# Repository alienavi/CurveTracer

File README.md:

# CurveTracer
This repository contains all the design files and code related to Semiconductor Curve Tracer made at CEDT, NSIT.
The different versions of Curve Tracer made are :

  - Analog Based (Oscillosccope Only)
  - Analog Based (with Arduino)
  - Arduino Only

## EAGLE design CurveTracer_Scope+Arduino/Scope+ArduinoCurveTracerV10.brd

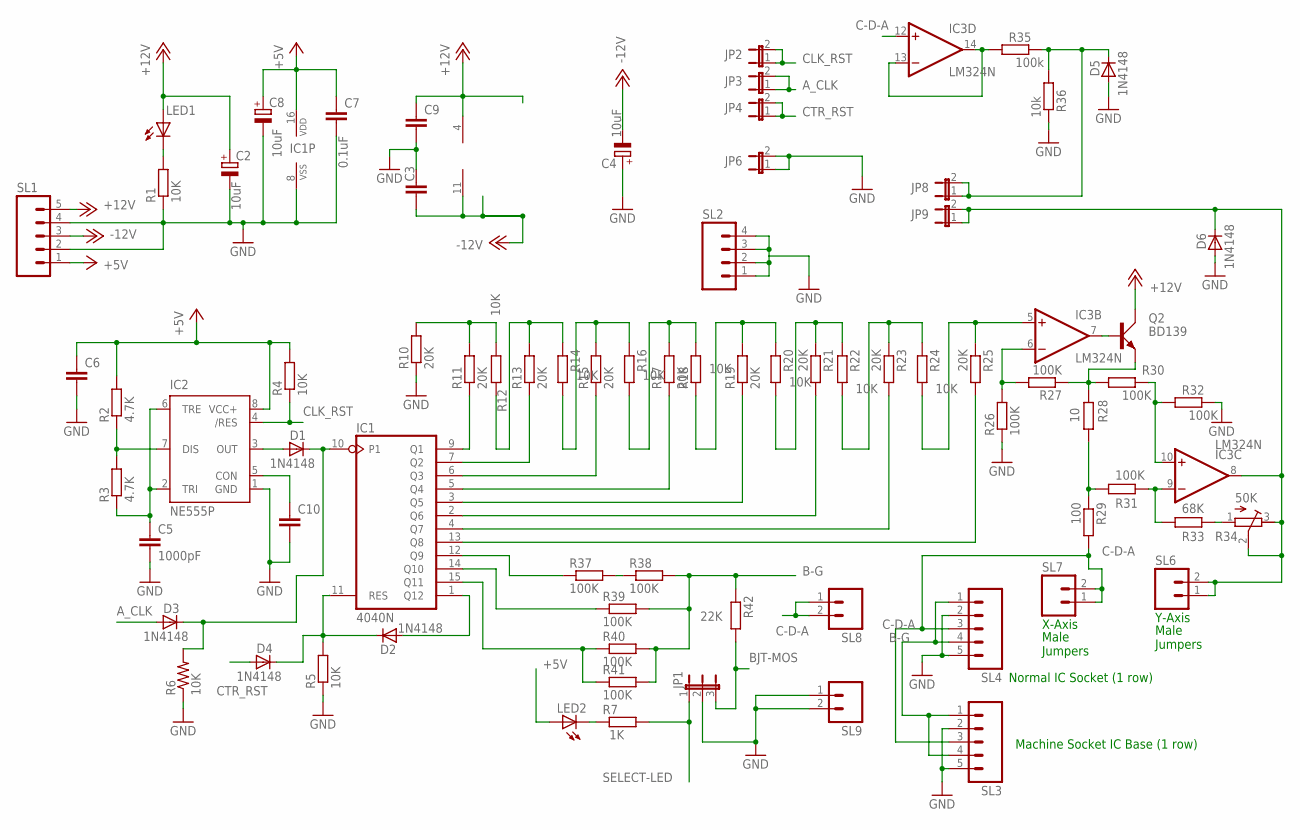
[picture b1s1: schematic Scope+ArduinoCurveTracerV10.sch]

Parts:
C2, C4, C8: 10uF; E2-5
C3, C6, C7, C9, C10: 0.1uF; C025-024X044
C5: 1000pF; C025-025X050
D1, D2, D3, D4, D5: 1N4148; DO35-7
D6: 1N4148; DO35-10
IC1: 4040N; DIL16
IC2: NE555P; DIL-08
IC3: LM324N; DIL14
JP1: JP2E; JP2
JP2, JP3, JP4, JP6, JP8, JP9: JP1E; JP1
LED1, LED2: LED3MM
Q2: BD139; TO126AV
R1, R4, R5, R6, R12, R14, R16, R18, R20, R22, R24: 10K; 0204/7
R2, R3: 4.7K; 0204/7
R7: 1K; 0204/7
R10, R11, R13, R15, R17, R19, R21, R23, R25: 20K; 0204/7
R26, R27, R31, R32, R37, R38, R39, R40, R41: 100K; 0204/7
R28: 10; 0207/10
R29: 100; 0309/12
R30: 100K; 0207/10
R33: 68K; 0204/7
R34: 50K; RTRIM64W
R35: 100k; 0204/7
R36: 10k; 0204/7
R42: 22K; 0204/7
SL1, SL3, SL4: M05; 05P
SL2: M04; 04P
SL6, SL7, SL8, SL9: M02; 02P

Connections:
+5V: C6.1, C7.1, C8.+, IC1.16 (VDD), IC2.8 (VCC+), LED2.A, R2.2, R4.2, SL1.1
+12V: C2.+, C9.1, IC3.4 (V+), LED1.A, Q2.C, SL1.5
-12V: C3.2, C4.-, IC3.11 (V-), SL1.3
A_CLK: D3.A, JP3.1, JP3.2
B-G: R38.2, R39.2, R40.2, R41.2, R42.1, SL3.1, SL3.4, SL4.1, SL4.4
BJT-MOS: JP1.3, R42.2
C-D-A: IC3.12 (+IN), R29.2, SL3.3, SL4.3, SL7.1, SL7.2, SL8.1, SL8.2
CLK_RST: IC2.4 (/RES), JP2.1, JP2.2, R4.1
CTR_RST: D4.A, JP4.1, JP4.2
GND: C2.-, C3.1, C4.+, C5.2, C6.2, C7.2, C8.-, C9.2, C10.2, D5.A, D6.A, IC1.8 (VSS), IC2.1 (GND), JP1.2, JP6.1, JP6.2, R1.1, R5.1, R6.1, R10.1, R26.1, R32.2, R36.2, SL1.2, SL1.4, SL2.1, SL2.2, SL2.3, SL2.4, SL3.2, SL3.5, SL4.2, SL4.5, SL9.1, SL9.2
unnamed: IC3.10 (+IN), R30.2, R32.1
unnamed: C10.1, IC2.5 (CON)
unnamed: R10.2, R11.2, R12.1
unnamed: D2.A, IC1.1 (Q12)
unnamed: R12.2, R13.2, R14.1
unnamed: R14.2, R15.2, R16.1
unnamed: R16.2, R17.2, R18.2
unnamed: R18.1, R19.2, R20.1
unnamed: R20.2, R21.1, R22.1
unnamed: IC1.9 (Q1), R11.1
unnamed: IC1.7 (Q2), R13.1
unnamed: IC1.6 (Q3), R15.1
unnamed: IC1.5 (Q4), R17.1
unnamed: IC1.3 (Q5), R19.1
unnamed: IC1.2 (Q6), R21.2
unnamed: IC1.4 (Q7), R23.2
unnamed: IC1.13 (Q8), R25.2
unnamed: R22.2, R23.1, R24.1
unnamed: IC3.5 (+IN), R24.2, R25.1
unnamed: R37.2, R38.1
unnamed: IC1.14 (Q10), R39.1
unnamed: IC1.12 (Q9), R37.1
unnamed: IC3.9 (-IN), R31.2, R33.1
unnamed: Q2.E, R27.1, R28.2, R30.1
unnamed: LED1.K (C), R1.2
unnamed: IC3.6 (-IN), R26.2, R27.2
unnamed: IC3.7 (OUT), Q2.B
unnamed: D1.C, D3.C, IC1.10 (P1), R6.2
unnamed: IC1.15 (Q11), R40.1, R41.1
unnamed: LED2.K (C), R7.1
unnamed: R28.1, R29.1, R31.1
unnamed: D1.A, IC2.3 (OUT)
unnamed: D2.C, D4.C, IC1.11 (RES), R5.2
unnamed: IC2.7 (DIS), R2.1, R3.2
unnamed: C5.1, IC2.2 (TRI), IC2.6 (TRE), R3.1
unnamed: D6.C, IC3.8 (OUT), JP9.1, JP9.2, R34.2 (S), R34.3 (A), SL6.1, SL6.2
unnamed: D5.C, JP8.1, JP8.2, R35.2, R36.1
unnamed: IC3.13 (-IN), IC3.14 (OUT), R35.1
unnamed: R33.2, R34.1 (E)
SELECT-LED: JP1.1, R7.2

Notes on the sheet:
X-Axis
Y-Axis
Male Jumpers
Machine Socket IC Base (1 row)
Normal IC Socket (1 row)

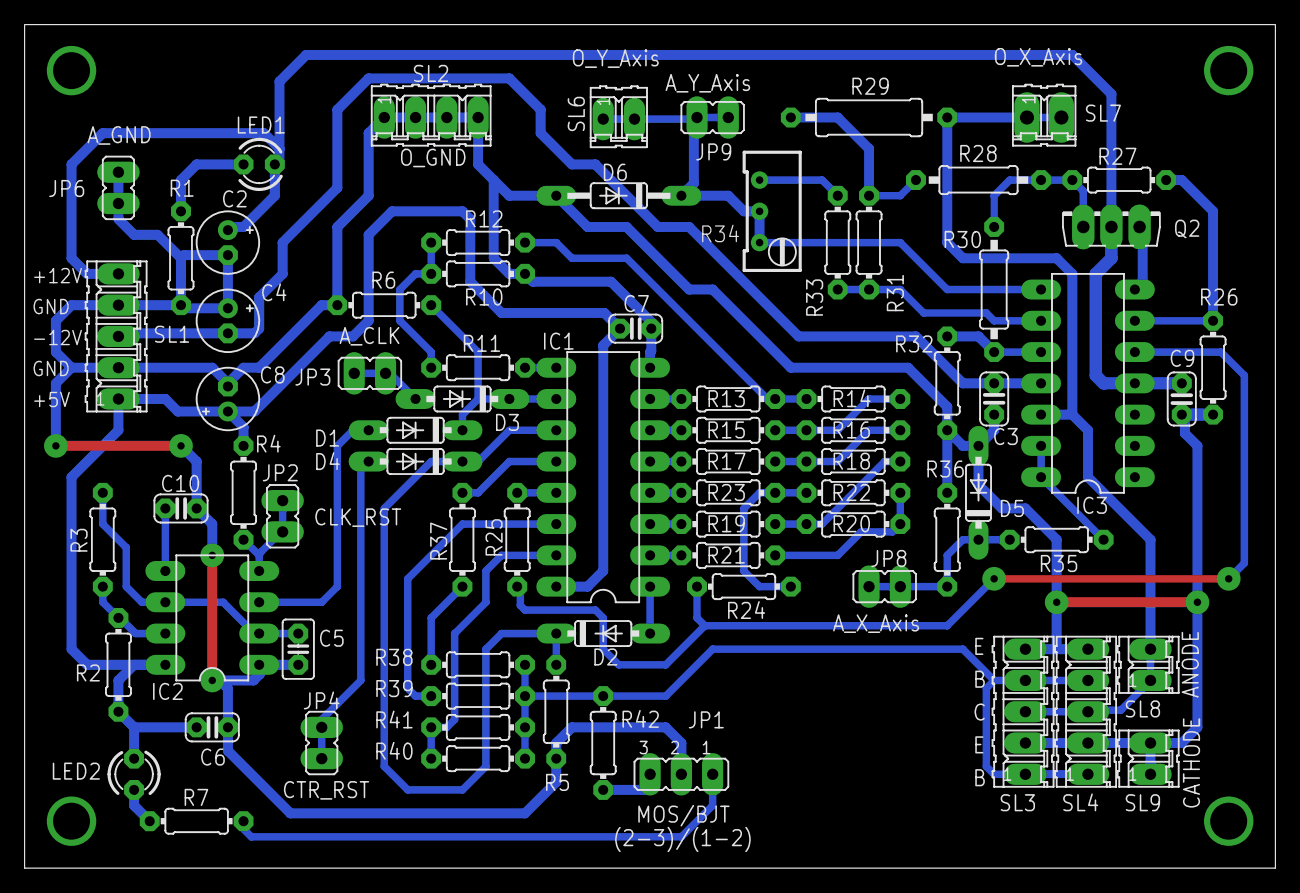
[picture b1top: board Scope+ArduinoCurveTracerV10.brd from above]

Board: 2 copper layers, 101.6 x 68.5 mm, 76 parts (0 on the bottom side), 50 nets.

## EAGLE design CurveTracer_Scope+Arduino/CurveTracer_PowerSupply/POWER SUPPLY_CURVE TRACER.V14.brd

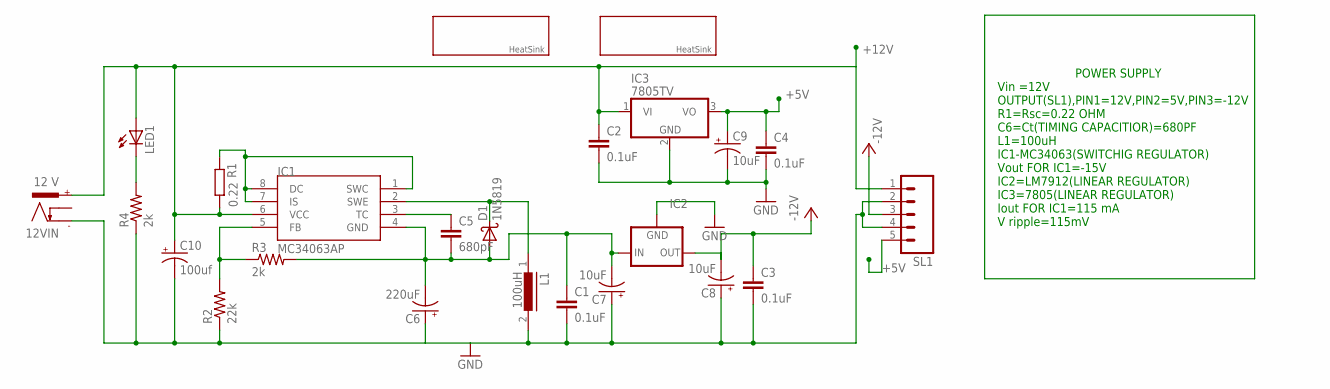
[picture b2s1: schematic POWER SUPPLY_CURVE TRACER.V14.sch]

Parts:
12VIN: 12 V; NEB21R
C1, C2, C3, C4: 0.1uF; C025-025X050
C5: 680pF; C025-025X050
C6: 220uF; E2,5-7
C7, C8, C9: 10uF; E2,5-6
C10: 100uf; E2,5-7
D1: 1N5819; DO41-10
IC1: MC34063AP; DIL08
IC2: 79XXS
IC3: 7805TV; TO220V
L1: 100uH; 82114R
LED1: LED3MM
R1: 0.22; 0617/17
R2: 22k; 0207/7
R3: 2k; 0204/7
R4: 2k; 0207/7
SL1: M05; 05P
U$1: HEATSINKMEDIUM; HEATSINK-MED
U$2: HEATSINKSMALL; HEATSINK-SML

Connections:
+5V: C4.1, C9.+, IC3.3 (VO), SL1.5
+12V: 12VIN.+, C2.1, C10.+, IC1.6 (VCC), IC3.1 (VI), LED1.A, R1.2, SL1.1
GND: 12VIN.-, C1.2, C2.2, C3.2, C4.2, C6.+, C7.+, C8.+, C9.-, C10.-, IC2.GND, IC3.2 (GND), L1.2, R2.1, R4.1, SL1.2, SL1.4
unnamed: IC1.5 (FB), R2.2, R3.1
unnamed: C1.1, C5.2, C6.-, C7.-, D1.A, IC1.4 (GND), IC2.IN, R3.2
unnamed: C5.1, IC1.3 (TC)
unnamed: D1.C, IC1.2 (SWE), L1.1
unnamed: LED1.K (C), R4.2
unnamed: IC1.1 (SWC), IC1.7 (IS), IC1.8 (DC), R1.1
VCC: C3.1, C8.-, IC2.OUT, SL1.3

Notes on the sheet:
POWER SUPPLY Vin =12V OUTPUT(SL1),PIN1=12V,PIN2=5V,PIN3=-12V R1=Rsc=0.22 OHM C6=Ct(TIMING CAPACITIOR)=680PF L1=100uH IC1-MC34063(SWITCHIG REGULATOR) Vout FOR IC1=-15V IC2=LM7912(LINEAR REGULATOR) IC3=7805(LINEAR REGULATOR) Iout FOR IC1=115 mA V ripple=115mV

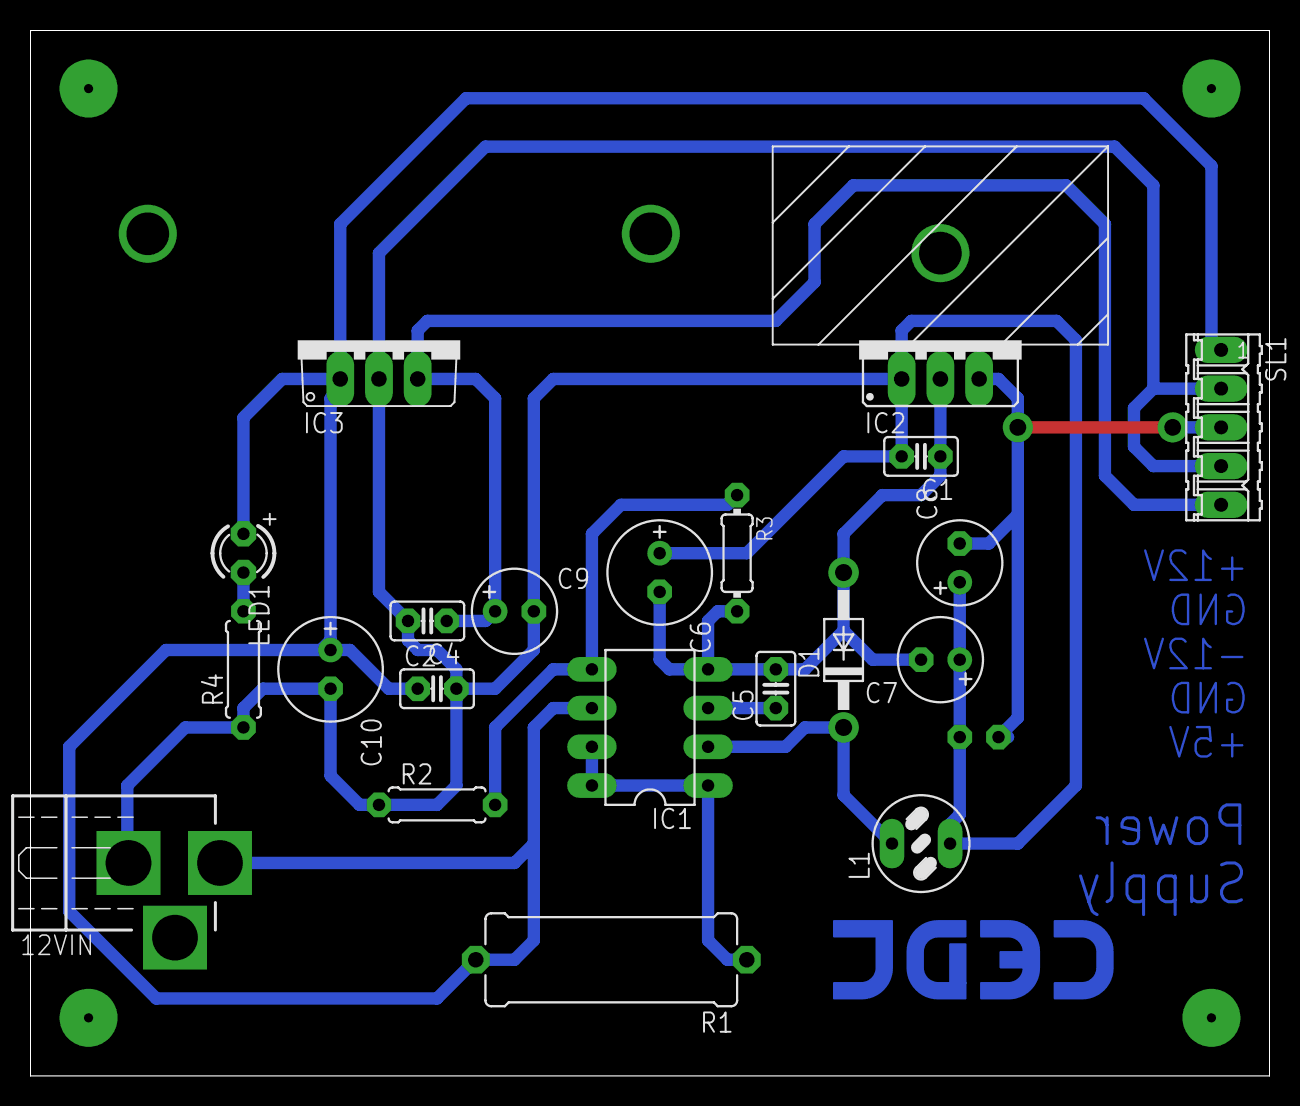
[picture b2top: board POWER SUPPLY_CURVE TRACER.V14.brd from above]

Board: 2 copper layers, 81.3 x 68.6 mm, 25 parts (1 on the bottom side), 10 nets.

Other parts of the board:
U$3: LOGO-CEDT-BOT-18MM

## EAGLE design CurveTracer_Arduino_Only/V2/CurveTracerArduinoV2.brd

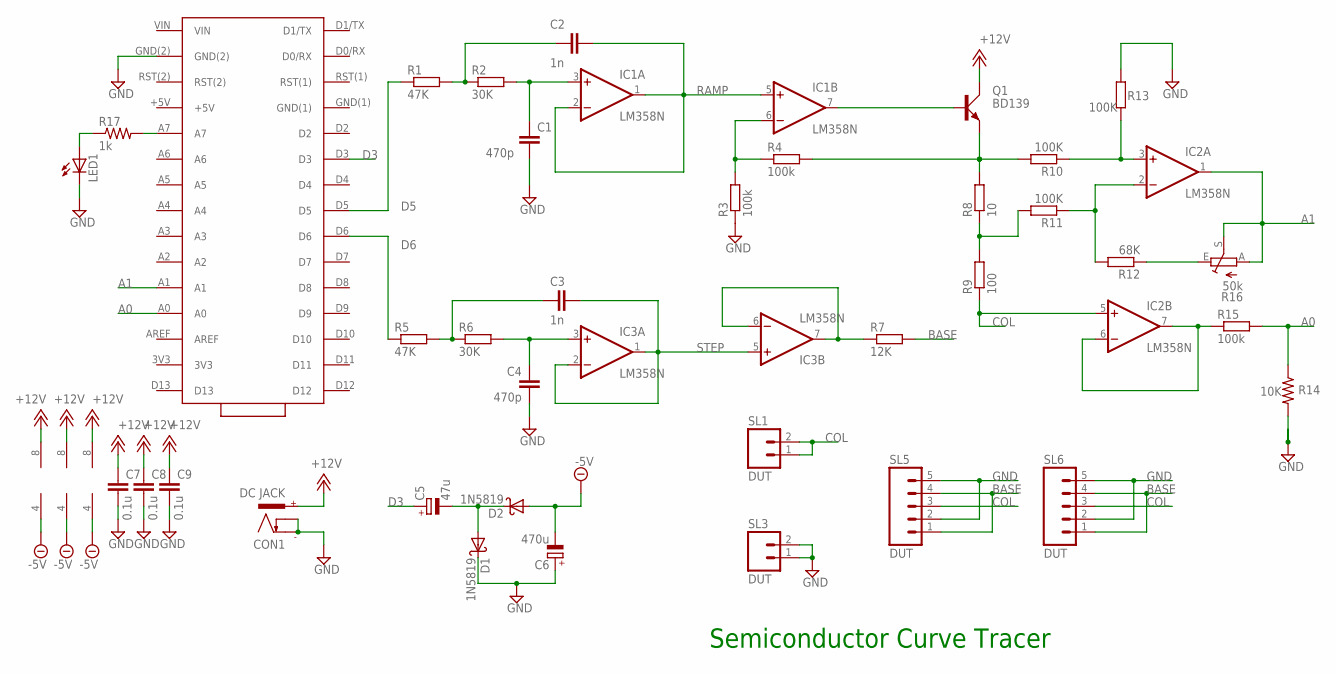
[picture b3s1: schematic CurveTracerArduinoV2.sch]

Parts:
C1, C4: 470p; C025-024X044
C2, C3: 1n; C025-024X044
C5: 47u; E2,5-5
C6: 470u; E2,5-5
C7, C8, C9: 0.1u; C025-024X044
CON1: DC JACK; NEB21R
D1, D2: 1N5819; DO41-10
IC1, IC2, IC3: LM358N; DIL08
LED1: RED LED; LED3MM
NANO: ARDUINO(NANO_3.0); ARDUINO_NANO_30PIN
Q1: BD139; TO126AV
R1: 47K; 0207/10
R2, R6: 30K; 0204/7
R3, R4: 100k; 0207/10
R5: 47K; 0204/7
R7: 12K; 0207/10
R8: 10; 0207/10
R9: 100; 0207/10
R10, R11: 100K; 0207/10
R12: 68K; 0204/7
R13: 100K; 0204/7
R14: 10K; 0207/10
R15: 100k; 0204/7
R16: 50k; S64W
R17: 1k; 0204/7
SL1, SL3: DUT; 02P
SL5, SL6: DUT; 05P

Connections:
+12V: C7.1, C8.1, C9.1, CON1.+, IC1.8 (V+), IC2.8 (V+), IC3.8 (V+), Q1.C
-5V: C6.-, D2.A, IC1.4 (V-), IC2.4 (V-), IC3.4 (V-)
A0: NANO.A0, R14.1, R15.2
A1: IC2.1 (OUT), NANO.A1, R16.A, R16.S
BASE: R7.2, SL5.1, SL5.4, SL6.1, SL6.4
COL: IC2.5 (+IN), R9.1, SL1.1, SL1.2, SL5.3, SL6.3
D3: C5.+, NANO.D3
D5: NANO.D5, R1.1
D6: NANO.D6, R5.1
GND: C1.2, C4.1, C6.+, C7.2, C8.2, C9.2, CON1.-, CON1.C, D1.C, LED1.K (C), NANO.GND(2), R3.1, R13.1, R14.2, SL3.1, SL3.2, SL5.2, SL5.5, SL6.2, SL6.5
unnamed: C5.-, D1.A, D2.C
unnamed: C2.1, R1.2, R2.1
unnamed: C1.1, IC1.3 (+IN), R2.2
unnamed: IC3.6 (-IN), IC3.7 (OUT), R7.1
unnamed: IC1.7 (OUT), Q1.B
unnamed: IC1.6 (-IN), R3.2, R4.1
unnamed: C3.1, R5.2, R6.1
unnamed: C4.2, IC3.3 (+IN), R6.2
unnamed: Q1.E, R4.2, R8.2, R10.2
unnamed: IC2.3 (+IN), R10.1, R13.2
unnamed: IC2.2 (-IN), R11.1, R12.2
unnamed: IC2.6 (-IN), IC2.7 (OUT), R15.1
unnamed: R12.1, R16.E
unnamed: R8.1, R9.2, R11.2
unnamed: LED1.A, R17.1
unnamed: NANO.A7, R17.2
RAMP: C2.2, IC1.1 (OUT), IC1.2 (-IN), IC1.5 (+IN)
STEP: C3.2, IC3.1 (OUT), IC3.2 (-IN), IC3.5 (+IN)

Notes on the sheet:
Semiconductor Curve Tracer

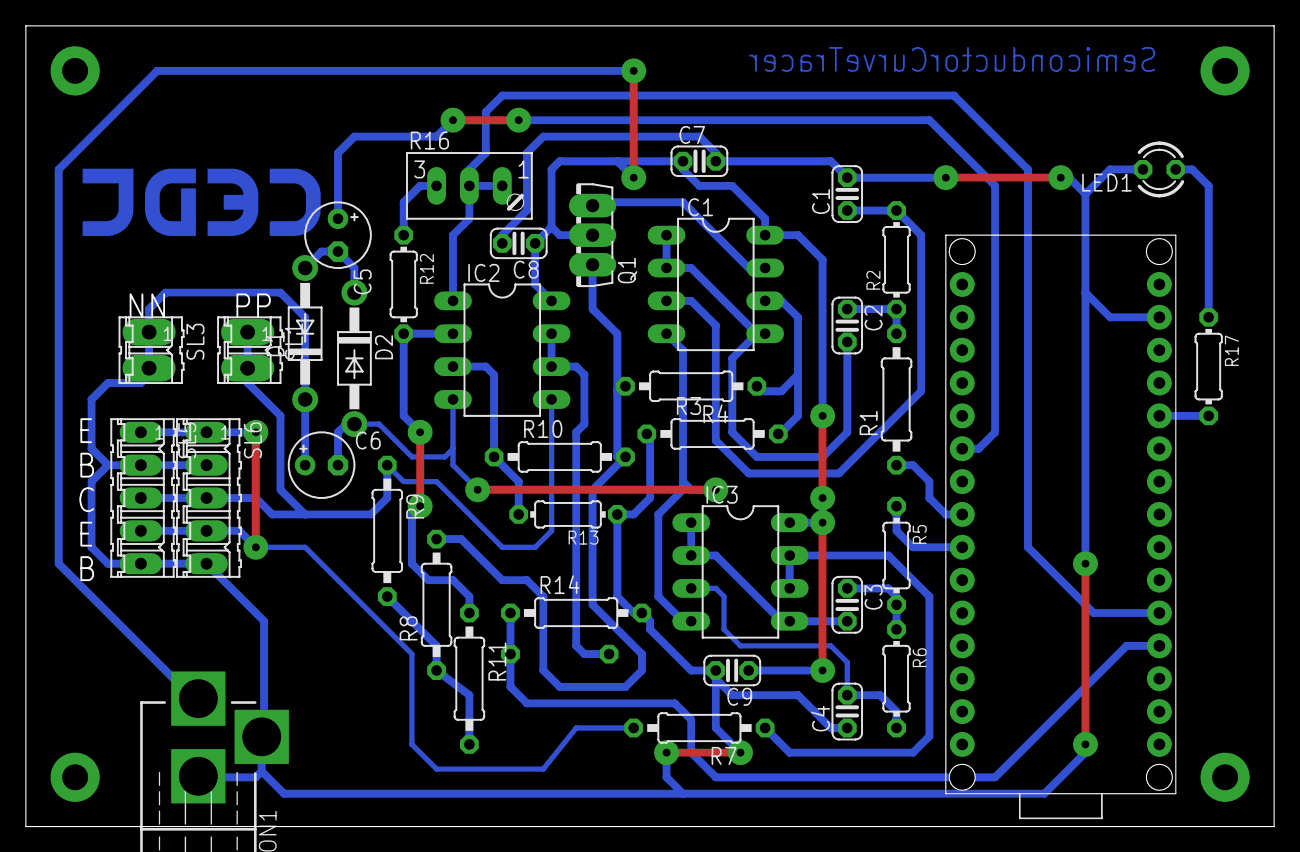
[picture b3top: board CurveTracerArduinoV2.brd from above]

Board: 2 copper layers, 96.5 x 61.9 mm, 40 parts (1 on the bottom side), 28 nets.

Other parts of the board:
U$2: LOGO-CEDT-BOT-18MM

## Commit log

2016-09-03 Curve Tracer Arduino Only

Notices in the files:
parts and their libraries:
SparkFun: Licensing: CC v3.0 Share-Alike You are welcome to use this library for commercial purposes.
